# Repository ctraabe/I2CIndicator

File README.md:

# I2CIndicator

An indicator board with several LEDs driven by the PCA9685 LED driver IC.

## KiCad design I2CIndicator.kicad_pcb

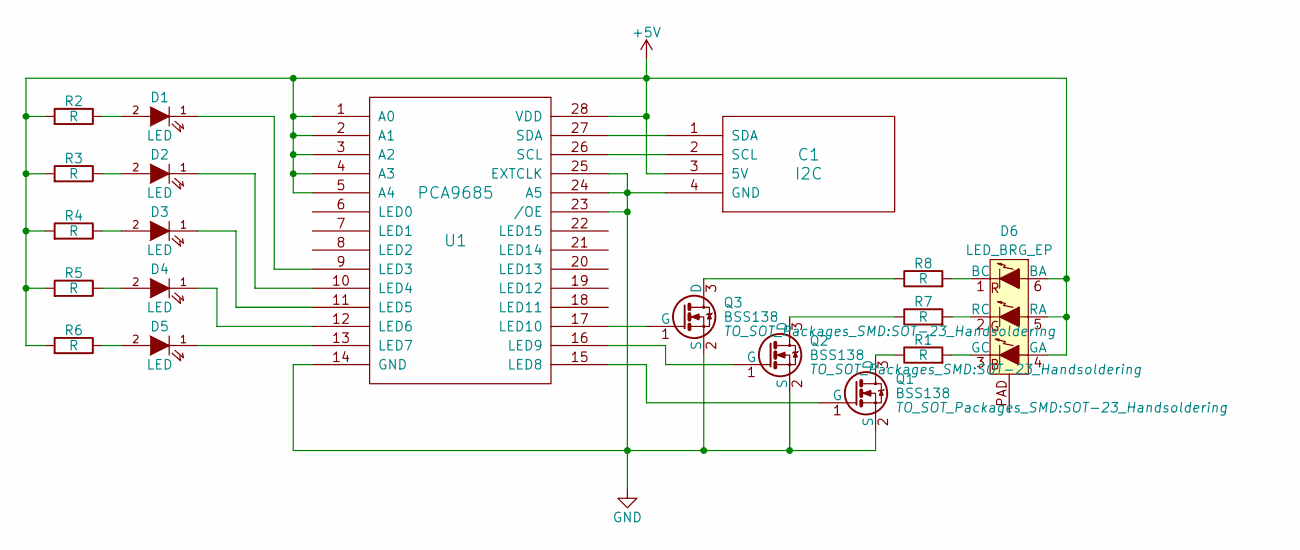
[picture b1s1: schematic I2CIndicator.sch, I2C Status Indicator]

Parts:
C1: I2C; Connector_Molex_PicoBlade_53047-0410
D1, D2, D3, D4, D5: LED; LED_0805
D6: LED_BRG_EP; SunLED-XZ
Q1, Q2, Q3: BSS138; SOT-23_Handsoldering
R1, R7, R8: R; Resistor_Horizontal_RM7mm
R2, R3, R4, R5, R6: R; R_0805_HandSoldering
U1: PCA9685; TSSOP-28_4.4x9.7mm_Pitch0.65mm

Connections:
+5V: C1.3 (5V), D6.4 (GA), D6.5 (RA), D6.6 (BA), R2.2, R3.2, R4.2, R5.2, R6.2, U1.1 (A0), U1.2 (A1), U1.3 (A2), U1.4 (A3), U1.5 (A4), U1.28 (VDD)
GND: C1.4 (GND), Q1.2 (S), Q2.2 (S), Q3.2 (S), U1.14 (GND), U1.23 (/OE), U1.24 (A5), U1.25 (EXTCLK)
unnamed: C1.1 (SDA), U1.27 (SDA)
unnamed: C1.2 (SCL), U1.26 (SCL)
unnamed: D1.1 (K), U1.9 (LED3)
unnamed: D1.2 (A), R2.1
unnamed: D2.1 (K), U1.10 (LED4)
unnamed: D2.2 (A), R3.1
unnamed: D3.1 (K), U1.11 (LED5)
unnamed: D3.2 (A), R4.1
unnamed: D4.1 (K), U1.12 (LED6)
unnamed: D4.2 (A), R5.1
unnamed: D5.1 (K), U1.13 (LED7)
unnamed: D5.2 (A), R6.1
unnamed: D6.1 (BC), R8.2
unnamed: D6.2 (RC), R7.2
unnamed: D6.3 (GC), R1.2
unnamed: Q1.1 (G), U1.15 (LED8)
unnamed: Q1.3 (D), R1.1
unnamed: Q2.1 (G), U1.16 (LED9)
unnamed: Q2.3 (D), R7.1
unnamed: Q3.1 (G), U1.17 (LED10)
unnamed: Q3.3 (D), R8.1

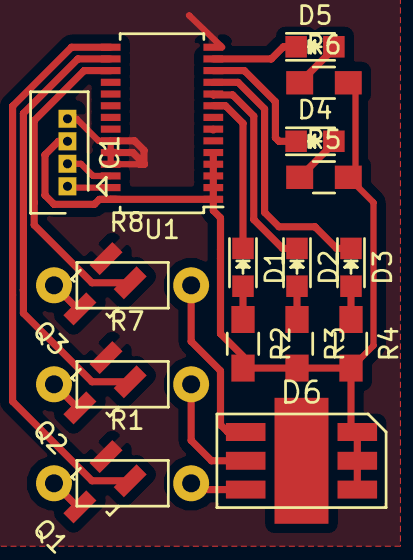
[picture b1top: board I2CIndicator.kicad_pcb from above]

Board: 2 copper layers, 19 parts (0 on the bottom side), 23 nets.

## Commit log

2016-11-25 Changed the name of the repository
2016-11-25 Added common libraries submodule
2016-11-25 Original version with FIXED OSRAM footprint
2016-11-25 Modified to use SunLED XZCB25MO24DG25X111S
2016-12-04 Found wrong component was used for N-MOSFET transistors resulting in wrong layout. Fixed schamatic, but layout needs to be fixed.
2016-12-05 Fixed the layout
